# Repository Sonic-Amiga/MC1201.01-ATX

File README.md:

# О проекте

Данный проект является реконструкцией материнской платы ДВК-1 МС1201.01 в современных
условиях. Основной особенностью дизайна является замена большинства дефицитных микросхем на
более доступные схемотехнические решения, а также использование формата ATX.

Изначальным автором проекта является Павел "MAX232CPE". Данную плату можно
[приобрести у автора](https://www.avito.ru/ufa/tovary_dlya_kompyutera/ms1201_atx_3347565757?slocation=653240&context=H4sIAAAAAAAA_wE_AMD_YToyOntzOjEzOiJsb2NhbFByaW9yaXR5IjtiOjA7czoxOiJ4IjtzOjE2OiI1Sm9XZU1sOTdqZFBkbVNuIjt9T0K7ED8AAAA).
Целью данного репозитория является предоставление более читаемой схемы, чем предоставил автор,
а также её аудит с целью выявления ошибок. Целью не являлось создание собственной печатной платы, поэтому
посадочные места для компонентов не верифицировались, хотя должны быть назначены верно.

Нумерация элементов на схеме выполнена таким образом, что её можно сопоставить с оригинальной схемой.
Резисторные сборки разделены на дискретные резисторы, их нумерация E<номер сборки>_<номер контакта>. Элементы,
содержащие в своём названии букву X (напр. DX8, RX10, и т. д.) взяты из схемы замены динамического ОЗУ на
статическое.

В справочных целях все оригинальные схемы и некоторую документацию можно найти в каталоге [docs](docs). Схемы
приведены в нескольких версиях для лучшей читаемости.

# Обнаруженные ошибки (ERRATA) для ревизии 0.1c.

Некоторые из этих ошибок требуют реализации дополнительных схем. С этой целью разработана мезонинная плата,
которая содержит отсутствующую логику управления памятью, а также буфера для внешней шины. Документация на
плату доступна в каталоге [Mezzanine_Rev_0.1C](Mezzanine_Rev_0.1C).

Примечание: м/С 74HCT4067 может оказаться сложно найти. Успешно протестирована замена на гораздо более популярную
74HC4067. На AliExpress / Ozon также доступна микросхема CD4067 в DIP24 корпусе, но на данный момент её применение
не увенчалось успехом. Эта проблема будет разобрана позднее.

- E0001: Отсутствует подтяжка на +5В  
В оригинальной схеме данная цепь имеет номер 26 и подтянута к +5В через резисторную сборку E6 вывод 9.  
Решение: Установить резистор 2.2K навесным монтажом.

- E0002: Не подключенный вход /R микросхемы DD44  
В оригинальной схеме этот вход тоже не подключен, однако логика подсказывает, что на него также нужна подтяжка к +5В.  
Решение: Входы DD44 постоянно подтянуты к +5В. В оригинальной схеме МС1201.01 на них поданы сигналы с силовой
системной шины, которая в данном варианте удалена. Не устанавливать микросхему DD44 т. к. она ничего не делает.

- E0003: Неверное подключение /RPLY  
В оригинальной схеме глобальный сигнал /RPLY заведён на вывод 2 микросхемы DD8 через буфер К531АП2П. Буфер был
удалён автором реплики вместе с силовой шиной, а вместе с ним и соединение. Синхронизация сигнала /RPLY по любому
фронту тактового сигнала необходима согласно документации на процессор.  
Решение: Сигнал /RPLY соединяется через буфер DD1 на мезонинной плате. При необходимости можно запустить компьютер
без этого буфера, для этого необходимо не устанавливать E5_4 и соединить вывод 2 DD8 с глобальной цепью /RPLY.
Подтяжка сигнала /RPLY при этом осуществляется резистором E4_3.

- E0004: Отсутствует подключение CSRAM
Нет связи между выводом 10 DX7 и выводом 3 DX9, а также нет резистора RX10. Данный сигнал разрешает выбор ОЗУ.
Решение: провести отсутствующую связь и установить резистор навесным монтажом.  

- E0005: Не подключенные входы микросхем DD5 и DD9  
В оригинальной схеме сюда подаётся сигнал LOCK с контроллера динамической памяти. Этот сигнал разрешает обращение
к системному ПЗУ, активный уровень высокий и управляется регистром режима памяти (описан ниже).
Решение: Недостающая логика реализована на мезонинной плате.

- E0006: Дублированный резистор подтяжки  
Резистор должен быть только один, второй добавлен по ошибке.  
Решение: устанавливать только один из двух резисторов.

- E0007: Перепутаны типы микросхем на шелкографии
На плате перепутаны местами маркировки типов микросхем DD20 и DD44.  
Решение: Устанавливать согласно принципиальной схеме

- E0008: Отсутствует декодер адресов системного окна
В оригинальной схеме по адресам 177600..177677 доступны 64 байта ОЗУ, используемые процессором для переключения
между пользовательским и пультовым режимами. Данные адреса обусловлены аппаратным строением процессора и не могут
быть изменены. Этот функционал также реализуется удалённым контроллером динамической памяти. Для правильной работы
необходима дополнительная дешифрация адресных линий A9..A6 при доступе к области 176000...177777. Схема подключения
SRAM была перенесена с МС1201.02, которая имеет другой менеджер памяти, там данная область отсутствует.
Решение: Недостающая логика реализована на мезонинной плате.

- E0009: Вывод 8 микросхемы 1801ВП1-065 соединён с +5В
В оригинальной схеме используется микросхема 035, имеющая некоторые отличия. В частности, вывод 8 используется для
выбора 5-битного слова. В варианте 065 данный вывод является выходом с открытым коллектором, говорящим о том, что
микросхема выбрана. Соединение его с +5В может привести к повреждению микросхемы при попытке обращения к ней.
Решение: отключить вывод от +5В, перерезав дорожку. Сам вывод может быть использован для диагностики (требуется
подтяжка к +5В).

- E0010: Кнопка Reset подключена неверно.
Сигнал /INIT является для процессора выходом и презназначен для сброса внешних устройств и замыкание его на
землю не вызывает перезапуск процессора. Рестарт процессора осуществляется путём сброса сигналов /DCLO и /ACLO.
Решение: подключить кнопку параллельно конденсатору C76. Можно воспользоваться монтажным полем для установки
2-контактного разъёма.

- E0011: Некорректное соединение /DSR и /RxD.
Активным уровнем для этих сигналов является 0. Согласно спецификации сигнал DSR в активном состоянии говорит о том,
что удалённое устройство присутствует, включено и готово к работе. 155ЛН2 - это инверторы с открытым коллектором.
Установка сигнала /DSR в активное состояние приводит к тому, что линия RxD оказывается постоянно посаженной на 0,
что препятствует передаче данных.
Решение: разорвать соединение между выводами 10 и 12 микросхемы DX_16, разрезав дорожку.

# Карта памяти платы

Все адреса восьмеричные.

Начало | Конец  | Размер | Описание
-------|--------|--------|---------
000000 | 157777 | 56 Кб  | Основное ОЗУ
160000 | 163777 | 2 Кб   | Системное ПЗУ (если установлен бит 2 или 3 регистра режима памяти), иначе расширенное ОЗУ
164000 | 173777 | 3.5 Кб | Системное ПЗУ (если установлен бит 3 регистра режима памяти), иначе расширенное ОЗУ
173000 | 173777 | 512 б  | Системное ПЗУ (отображается всегда)
174000 | 175777 | 1 кб   | Расширенное ОЗУ
176000 | 176557 | 880 б  | Свободная область MMIO
176560 | 176567 | 8 б    | Второй последовательный порт
177560 | 177567 | 8 б    | Первый последовательный порт
177570 | 177577 | 8 б    | Свободная область MMIO
177600 | 177677 | 64 б   | Системное ОЗУ
177700 | 177716 | 16 б   | Внутренние регистры процессора (периферийный блок)
177714 |        |        | Внешний регистр ЦП 2 (/SEL2)
177716 |        |        | Внешний регистр ЦП 1 (/SEL1), регистр начального пуска, регистр режима памяти

Регистр 177716 используется одновременно для нескольких нужд и имеет следующую конфигурацию:

Бит    | 15 | 14 | 13 | 12 | 11 | 10 | 9 | 8 | 7 | 6 | 5 | 4 | 3  | 2  | 1 | 0
-------|----|----|----|----|----|----|---|---|---|---|---|---|----|----|---|---
Чтение | 1  | 1  | 1  | 0  | 0  | 0  | 0 | 0 | 0 | 0 | 0 | 0 |  a | M2 | b | c
Запись | -  | -  | -  | -  | -  | -  | - | - | - | - | - | - | M3 | M2 | - | -

- Биты 15 - 8 задают адрес начального пуска 160000.
- M3, M2 - биты регистра режима памяти
- a, b, c - биты, определяемые перемычками SA1. Если перемычка, соответствующая биту 3, не установлена, то
в позиции a будет считываться бит M3 регистра режима.

# Конфиурирование адресов ОЗУ

## Основное ОЗУ

Основное ОЗУ (адреса 000000 - 157777) разбито на банки по 8 Кб, каждый из которых может быть запрещён путём
установки перемычки J2. Если перемычка снята - банк доступен. Отключение банка требуется при установке
пользовательского ПЗУ, которое занимает тот же банк.

Обратный порядок перемычек обусловлен тем, что адреса передаются по шине в инвертированном виде.

Начало | Конец  | Биты 15..13 | Перемычка | Примечание
-------|--------|-------------|-----------|-----------
000000 | 017777 | 000         | 15-16     |
020000 | 037777 | 001         | 13-14     |
040000 | 057777 | 010         | 11-12     |
060000 | 077777 | 011         |  9-10     |
100000 | 117777 | 100         |  7-8      |
120000 | 137777 | 101         |  5-6      |
140000 | 157777 | 110         |  3-4      |
160000 | 177777 | 111         |  1-2      | Не устанавливать

## Расширенное ОЗУ

Расширенное ОЗУ (адреса 160000 - 175777) разбито на банки по 1 Кб, каждый из которых может быть запрещён путём
установки перемычки J1. Если перемычка снята - банк доступен. Формально по стандарту DEC адреса начиная с 160000
зарезервированы под внешние устройстка, поэтому отключение банка может потребоваться в случае
подключения внешних устройств, использующих те же адреса, что и банк.

Начало  | Конец  | Биты 12..10 | Перемычка | Примечание
--------|--------|-------------|-----------|-----------
160000  | 161777 | 000         | 15-16     |
162000  | 163777 | 001         | 13-14     |
164000  | 165777 | 010         | 11-12     |
166000  | 167777 | 011         |  9-10     |
170000  | 171777 | 100         |  7-8      |
172000  | 173777 | 101         |  5-6      | Доступно только 512 байтов, адреса 173000 - 173777 заняты ПЗУ
174000  | 175777 | 110         |  3-4      |
176000  | 177777 | 111         |  1-2      | Не устанавливать

## Перемычка J3

В данной плате схема подключения ОЗУ была полностью скопирована с существовавшей ранее универсальной схемы замены
ОЗУ для машин начиная с МС1202 (ДВК-2), поэтому в ней также присутствуют перемычки J3, предназначенные для адаптации
к различным машинам. В данной плате единственный вариант конфигурации предполагает соединение контактов 1 и 2. Это
соединение можно запаять жёстко, его переключение не предполагается. Остальные перемычки J3 использованию не подлежат,
поэтому разъём под них можно не устанавливать вовсе.

# Конфигурирование последовательного порта

Задание режимов работы последовательного порта производится перемычками S2. В таблицах ниже значение 0
соответствует установленной перемычке, 1 - снятой.

#### Перемычка 1-2 - выбор базового адреса и векторов прерывания
| Значение | Базовый адрес | Вектора прерывания приемника/передатчика |
|----------|---------------|------------------------------------------|
| 0        | 177560        | 060/064                                  |
| 1        | 176560        | 360/364                                  |

#### Выбор формата обмена по последовательному каналу
| Перемычка | 0                                | 1                              |
|-----------|----------------------------------|--------------------------------|
| 3-4       | 7 бит данных в слове             | 8 бит данных в слове           |
| 5-6       | формировать и проверять четность | не использовать бит четности   |
| 7-8       | контроль по четности             | контроль по нечетности         |

#### Перемычки 15-16, 13-14, 11-12, 9-10 - выбор скорости обмена по последовательному каналу
| Значение | Скорость обмена
|----------|----------------
| 0000     | 50
| 0001     | 75
| 0010     | 100
| 0011     | 150
| 0100     | 200
| 0101     | 300
| 0110     | 600
| 0111     | 1200
| 1000     | 2400
| 1001     | 4800
| 1010     | 9600
| 1011     | 19200
| 1100     | 57600
| 1101     | останов
| 1110     | останов
| 1111     | останов

Количество стоп-битов всегда равно двум, хотя при приёме проверяется только один. Для надёжной работы приёмника
рекомендуется выставлять на терминале 2 стоп-бита.

# Отладка

## Пошаговая отладка с помощью стенда.

Во время отладки я использовал [универсальную плату ввода-вывода](https://github.com/Sonic-Amiga/VersatileDebugBoard).
Тестовые сценарии к ней написаны на python и доступны в каталоге [Test_Scripts](Test_Scripts). Схема подключения
портов платы указана ниже. Все сигналы, если не указано иное, можно подать на системный разъём.

* Порт A0 - AD7...AD0
* Порт A1 - AD15...AD8
* Порт A2 - выходные сигналы управления:
    * bit0 - /SYNC
    * bit1 - /DIN - подавать на вывод 1 микросхемы DD6
    * bit2 - /DOUT
    * bit3 - /SEL1
* Порт C0 - Входные сигналы управления:
    * bit 0 - /RPLY

Блокировка процессора, если он уже установлен, осуществляется путём снятия перемычки S15 (/ACLO) и соединения вывода
29 процессора с землёй (через неё же). Сигнал /DCLO нужно оставить подключённым, иначе процессор не снимет 0 с линии
/INIT, заблокировав таким образом регистр управления памятью и последовательный порт.

Данные сценарии позволяют также проверить собранный [РЕ-мулятор](https://github.com/1801BM1/remul). При его подключении напрямую к стенду необходима
установка резисторов подтяжки к +5В сопротивлением 2.2К на все линии AD, а также на /RPLY. Вход /CE РЕ-мулятора
при этом соединяется с землёй.

!!! Учтите !!!, что К1801ВП1-065 реализует аппаратное управление потоком RTS/CTS. Если сигнал CTS от удалённого
устройства неактивен, то флаг готовности передатчика не выставляется, и тестовый сценарий будет бесконечно ждать
готовности, которая никогда не наступит. Дешёвые кабели USB-Serial могут не реализовывать эту линию. В этом случае
хотя-бы соедините RTS и CTS со стороны платы между собой (вам в любом случае понадобится нуль-модемный адаптер для
соединения с ПК с эмулятором терминала). То же самое относится и к работе программы из ПЗУ. Если вам кажется, что
машина висит, проверьте прохождение сигнала CTS.

## Тестирование с помощью тест-ПЗУ

Для финальной проверки и доводки собранной машины я написал специальное тест-ПЗУ. Его можно записать в РЕ-мулятор и
проверить вашу машину. Исходники доступны в каталоге [Test_ROM](Test_ROM).

Для сборки Вам потребуются:

* [Кросс-ассемблер MACRO-11](https://github.com/j-hoppe/MACRO11)
* [Линкер](https://github.com/AK6DN/obj2bin)
* [Утилита rev16.py](https://github.com/1801BM1/k1801/tree/master/rom/rev16_py)
* [Утилита srec_cat](https://srecord.sourceforge.net/)

Я собираю из-под Windows с использованием окружения MSYS2. Все вышеозначенные инструменты должны быть доступны в $PATH.

# Благодарности

* Павлу "MAX232CPE" за замечательный проект.
* 1801BM1@gmail.com за [исчерпывающую документацию на процессор](https://forum.maxiol.com/index.php?act=attach&type=post&id=10512).
* Oleksandr Kovalenko за [библиотеку элементов для KiCad](https://github.com/alk0v/KiCad-Lib-ussr-elements).
* Vslav за [документацию на К1801ВП1](https://github.com/1801BM1/k1801) и [проект РЕ-мулятора](https://github.com/1801BM1/remul).
* Jörg Hoppe за порт MACRO-11
* Don North за кросс-платформенный линковщик

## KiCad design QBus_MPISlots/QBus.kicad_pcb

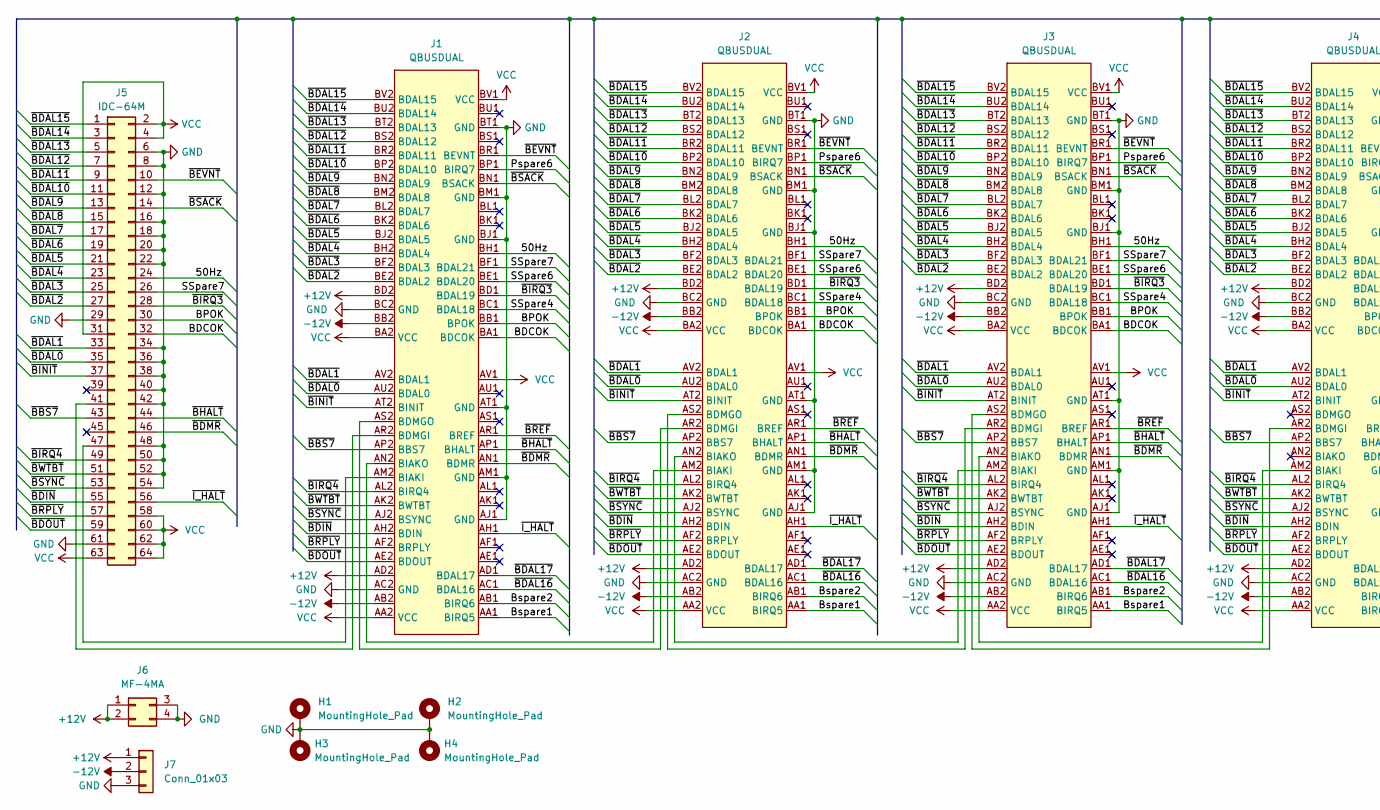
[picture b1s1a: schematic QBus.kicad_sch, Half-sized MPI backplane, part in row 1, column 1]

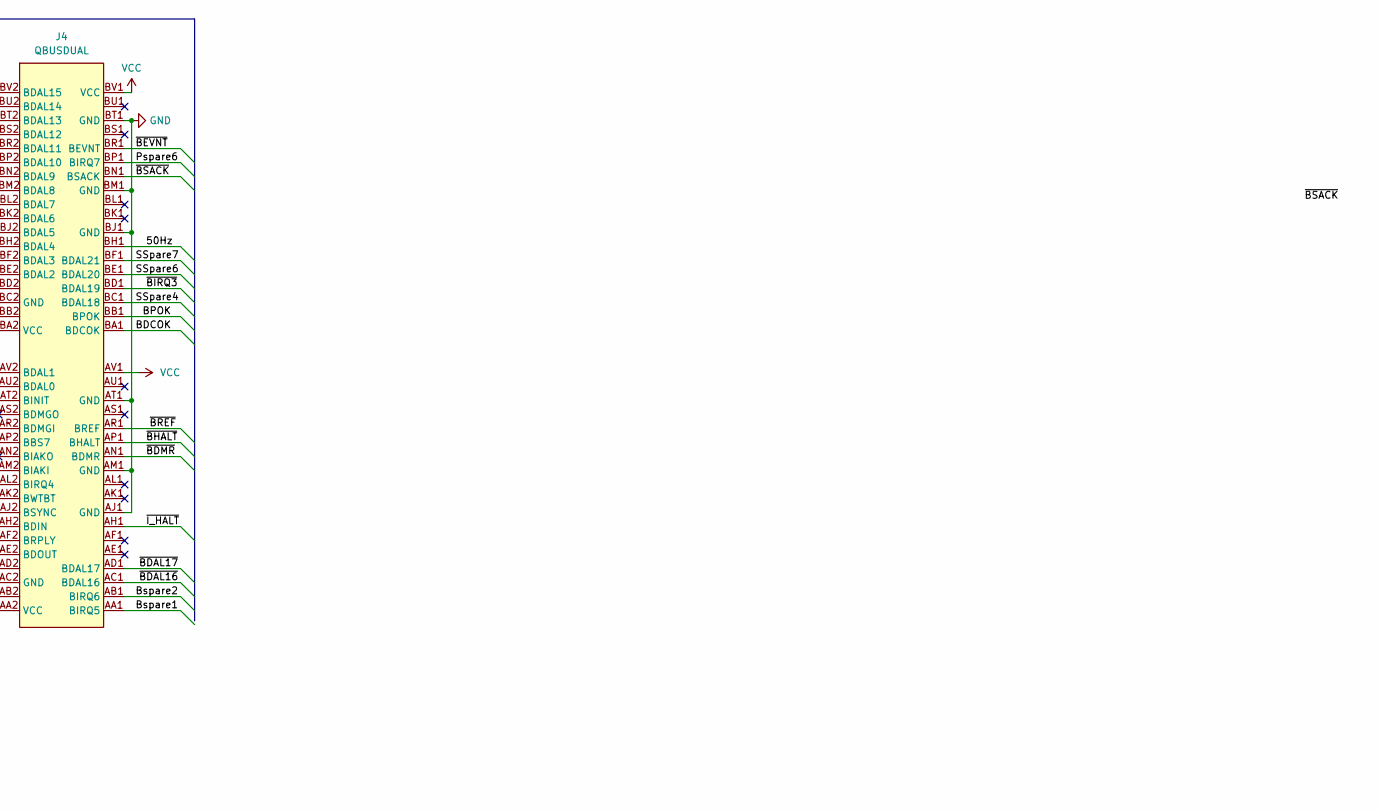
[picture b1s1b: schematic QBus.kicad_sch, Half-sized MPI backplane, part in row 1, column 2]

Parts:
H1, H2, H3, H4: MountingHole_Pad; MountingHole_3.5mm_Pad
J1, J2, J3, J4: QBUSDUAL; RPPM16x72
J5: IDC-64M; IDC-Header_2x32_P2.54mm_Vertical
J6: MF-4MA; Molex_Mini-Fit_Jr_5566-04A_2x02_P4.20mm_Vertical
J7: Conn_01x03; Wago_734-133_1x03_P3.50mm_Vertical

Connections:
+12V: J1.AD2, J1.BD2, J2.AD2, J2.BD2, J3.AD2, J3.BD2, J4.AD2, J4.BD2, J6.1, J6.2, J7.1
-12V: J1.AB2, J1.BB2, J2.AB2, J2.BB2, J3.AB2, J3.BB2, J4.AB2, J4.BB2, J7.2
/50Hz: J1.BH1, J2.BH1, J3.BH1, J4.BH1, J5.24
/BDCOK: J1.BA1 (BDCOK), J2.BA1 (BDCOK), J3.BA1 (BDCOK), J4.BA1 (BDCOK), J5.32
/BPOK: J1.BB1 (BPOK), J2.BB1 (BPOK), J3.BB1 (BPOK), J4.BB1 (BPOK), J5.30
/Bspare1: J1.AA1 (BIRQ5), J2.AA1 (BIRQ5), J3.AA1 (BIRQ5), J4.AA1 (BIRQ5)
/Bspare2: J1.AB1 (BIRQ6), J2.AB1 (BIRQ6), J3.AB1 (BIRQ6), J4.AB1 (BIRQ6)
/Pspare6: J1.BP1 (BIRQ7), J2.BP1 (BIRQ7), J3.BP1 (BIRQ7), J4.BP1 (BIRQ7)
/SSpare4: J1.BC1 (BDAL18), J2.BC1 (BDAL18), J3.BC1 (BDAL18), J4.BC1 (BDAL18)
/SSpare6: J1.BE1 (BDAL20), J2.BE1 (BDAL20), J3.BE1 (BDAL20), J4.BE1 (BDAL20)
/SSpare7: J1.BF1 (BDAL21), J2.BF1 (BDAL21), J3.BF1 (BDAL21), J4.BF1 (BDAL21), J5.26
/~BBS7: J1.AP2 (BBS7), J2.AP2 (BBS7), J3.AP2 (BBS7), J4.AP2 (BBS7), J5.43
/~BDAL0: J1.AU2 (BDAL0), J2.AU2 (BDAL0), J3.AU2 (BDAL0), J4.AU2 (BDAL0), J5.35
/~BDAL1: J1.AV2 (BDAL1), J2.AV2 (BDAL1), J3.AV2 (BDAL1), J4.AV2 (BDAL1), J5.33
/~BDAL2: J1.BE2 (BDAL2), J2.BE2 (BDAL2), J3.BE2 (BDAL2), J4.BE2 (BDAL2), J5.27
/~BDAL3: J1.BF2 (BDAL3), J2.BF2 (BDAL3), J3.BF2 (BDAL3), J4.BF2 (BDAL3), J5.25
/~BDAL4: J1.BH2 (BDAL4), J2.BH2 (BDAL4), J3.BH2 (BDAL4), J4.BH2 (BDAL4), J5.23
/~BDAL5: J1.BJ2 (BDAL5), J2.BJ2 (BDAL5), J3.BJ2 (BDAL5), J4.BJ2 (BDAL5), J5.21
/~BDAL6: J1.BK2 (BDAL6), J2.BK2 (BDAL6), J3.BK2 (BDAL6), J4.BK2 (BDAL6), J5.19
/~BDAL7: J1.BL2 (BDAL7), J2.BL2 (BDAL7), J3.BL2 (BDAL7), J4.BL2 (BDAL7), J5.17
/~BDAL8: J1.BM2 (BDAL8), J2.BM2 (BDAL8), J3.BM2 (BDAL8), J4.BM2 (BDAL8), J5.15
/~BDAL9: J1.BN2 (BDAL9), J2.BN2 (BDAL9), J3.BN2 (BDAL9), J4.BN2 (BDAL9), J5.13
/~BDAL10: J1.BP2 (BDAL10), J2.BP2 (BDAL10), J3.BP2 (BDAL10), J4.BP2 (BDAL10), J5.11
/~BDAL11: J1.BR2 (BDAL11), J2.BR2 (BDAL11), J3.BR2 (BDAL11), J4.BR2 (BDAL11), J5.9
/~BDAL12: J1.BS2 (BDAL12), J2.BS2 (BDAL12), J3.BS2 (BDAL12), J4.BS2 (BDAL12), J5.7
/~BDAL13: J1.BT2 (BDAL13), J2.BT2 (BDAL13), J3.BT2 (BDAL13), J4.BT2 (BDAL13), J5.5
/~BDAL14: J1.BU2 (BDAL14), J2.BU2 (BDAL14), J3.BU2 (BDAL14), J4.BU2 (BDAL14), J5.3
/~BDAL15: J1.BV2 (BDAL15), J2.BV2 (BDAL15), J3.BV2 (BDAL15), J4.BV2 (BDAL15), J5.1
/~BDAL16: J1.AC1 (BDAL16), J2.AC1 (BDAL16), J3.AC1 (BDAL16), J4.AC1 (BDAL16)
/~BDAL17: J1.AD1 (BDAL17), J2.AD1 (BDAL17), J3.AD1 (BDAL17), J4.AD1 (BDAL17)
/~BDIN: J1.AH2 (BDIN), J2.AH2 (BDIN), J3.AH2 (BDIN), J4.AH2 (BDIN), J5.55
/~BDMR: J1.AN1 (BDMR), J2.AN1 (BDMR), J3.AN1 (BDMR), J4.AN1 (BDMR), J5.46
/~BDOUT: J1.AE2 (BDOUT), J2.AE2 (BDOUT), J3.AE2 (BDOUT), J4.AE2 (BDOUT), J5.59
/~BEVNT: J1.BR1 (BEVNT), J2.BR1 (BEVNT), J3.BR1 (BEVNT), J4.BR1 (BEVNT), J5.10
/~BHALT: J1.AP1 (BHALT), J2.AP1 (BHALT), J3.AP1 (BHALT), J4.AP1 (BHALT), J5.44
/~BINIT: J1.AT2 (BINIT), J2.AT2 (BINIT), J3.AT2 (BINIT), J4.AT2 (BINIT), J5.37
/~BIRQ3: J1.BD1 (BDAL19), J2.BD1 (BDAL19), J3.BD1 (BDAL19), J4.BD1 (BDAL19), J5.28
/~BIRQ4: J1.AL2 (BIRQ4), J2.AL2 (BIRQ4), J3.AL2 (BIRQ4), J4.AL2 (BIRQ4), J5.49
/~BREF: J1.AR1 (BREF), J2.AR1 (BREF), J3.AR1 (BREF), J4.AR1 (BREF)
/~BRPLY: J1.AF2 (BRPLY), J2.AF2 (BRPLY), J3.AF2 (BRPLY), J4.AF2 (BRPLY), J5.57
/~BSACK: J1.BN1 (BSACK), J2.BN1 (BSACK), J3.BN1 (BSACK), J4.BN1 (BSACK), J5.14
/~BSYNC: J1.AJ2 (BSYNC), J2.AJ2 (BSYNC), J3.AJ2 (BSYNC), J4.AJ2 (BSYNC), J5.53
/~BWTBT: J1.AK2 (BWTBT), J2.AK2 (BWTBT), J3.AK2 (BWTBT), J4.AK2 (BWTBT), J5.51
/~I_HALT: J1.AH1, J2.AH1, J3.AH1, J4.AH1, J5.56
GND: H1.1 (1_1), H2.1 (1_1), H3.1 (1_1), H4.1 (1_1), J1.AC2 (GND), J1.AJ1 (GND), J1.AM1 (GND), J1.AT1 (GND), J1.BC2 (GND), J1.BJ1 (GND), J1.BM1 (GND), J1.BT1 (GND), J2.AC2 (GND), J2.AJ1 (GND), J2.AM1 (GND), J2.AT1 (GND), J2.BC2 (GND), J2.BJ1 (GND), J2.BM1 (GND), J2.BT1 (GND), J3.AC2 (GND), J3.AJ1 (GND), J3.AM1 (GND), J3.AT1 (GND), J3.BC2 (GND), J3.BJ1 (GND), J3.BM1 (GND), J3.BT1 (GND), J4.AC2 (GND), J4.AJ1 (GND), J4.AM1 (GND), J4.AT1 (GND), J4.BC2 (GND), J4.BJ1 (GND), J4.BM1 (GND), J4.BT1 (GND), J5.6, J5.8, J5.12, J5.16, J5.18, J5.20, J5.22, J5.29, J5.34, J5.36, J5.38, J5.40, J5.42, J5.48, J5.50, J5.52, J5.54, J5.61, J6.3, J6.4, J7.3
unnamed: J1.AR2 (BDMGI), J5.41
unnamed: J1.AS2 (BDMGO), J2.AR2 (BDMGI)
unnamed: J1.AM2 (BIAKI), J5.47
unnamed: J1.AN2 (BIAKO), J2.AM2 (BIAKI)
unnamed: J2.AS2 (BDMGO), J3.AR2 (BDMGI)
unnamed: J2.AN2 (BIAKO), J3.AM2 (BIAKI)
unnamed: J3.AS2 (BDMGO), J4.AR2 (BDMGI)
unnamed: J3.AN2 (BIAKO), J4.AM2 (BIAKI)
VCC: J1.AA2 (VCC), J1.AV1, J1.BA2 (VCC), J1.BV1 (VCC), J2.AA2 (VCC), J2.AV1, J2.BA2 (VCC), J2.BV1 (VCC), J3.AA2 (VCC), J3.AV1, J3.BA2 (VCC), J3.BV1 (VCC), J4.AA2 (VCC), J4.AV1, J4.BA2 (VCC), J4.BV1 (VCC), J5.2, J5.4, J5.31, J5.58, J5.60, J5.62, J5.63, J5.64

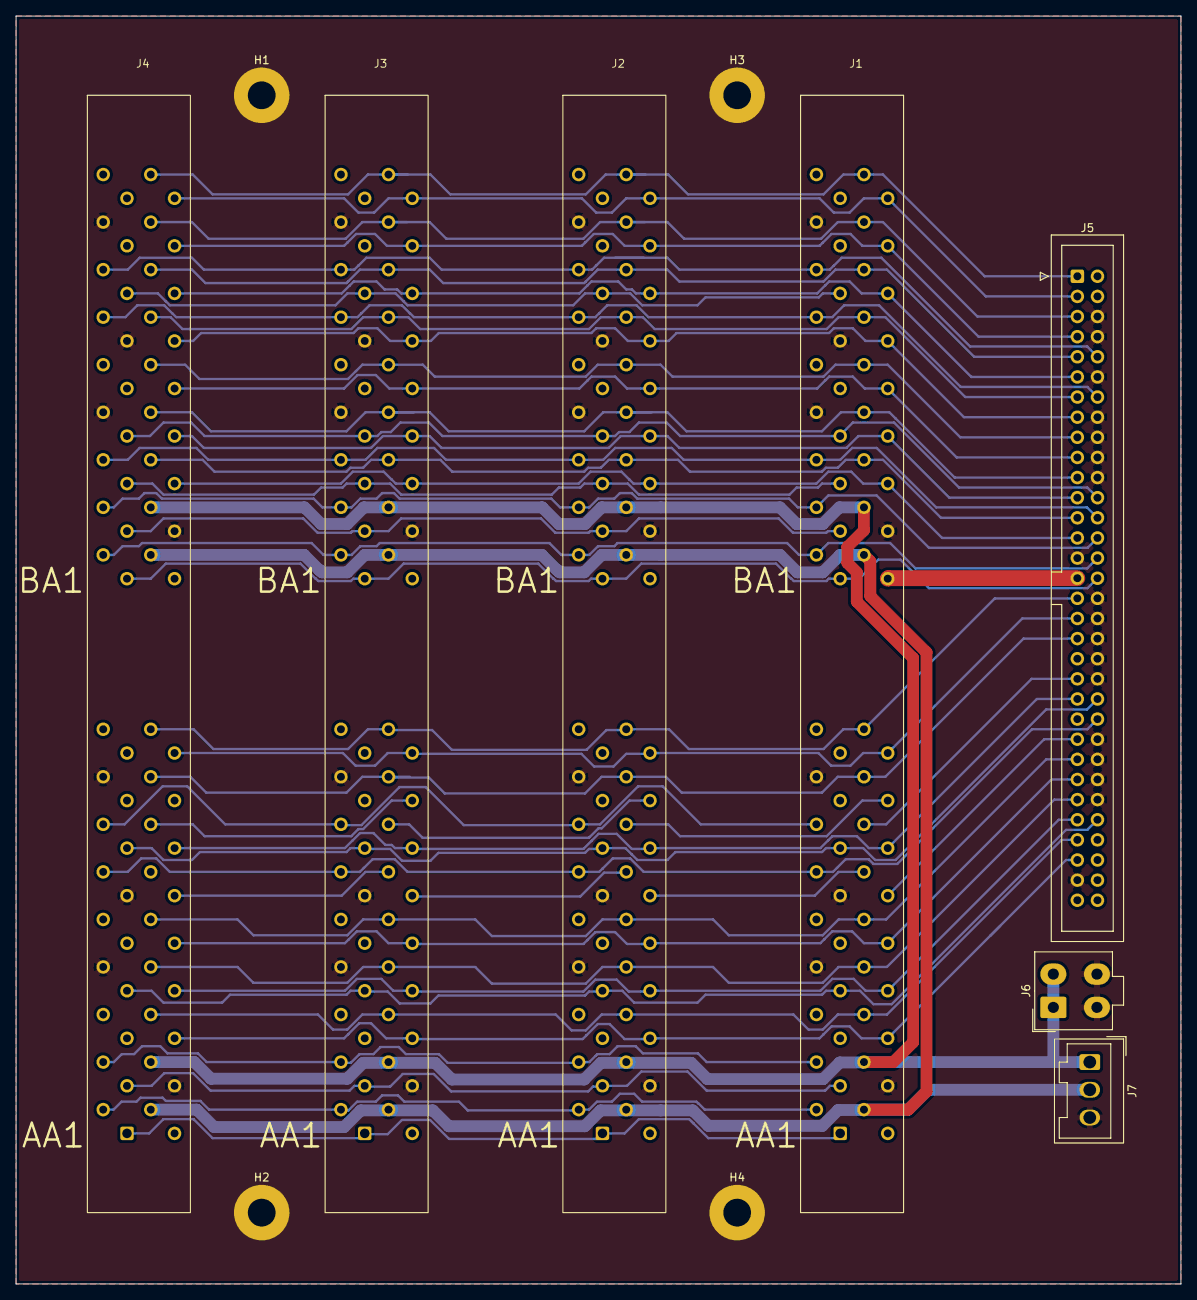
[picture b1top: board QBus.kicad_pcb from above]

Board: 2 copper layers, 147.0 x 160.0 mm, 11 parts (0 on the bottom side), 54 nets.

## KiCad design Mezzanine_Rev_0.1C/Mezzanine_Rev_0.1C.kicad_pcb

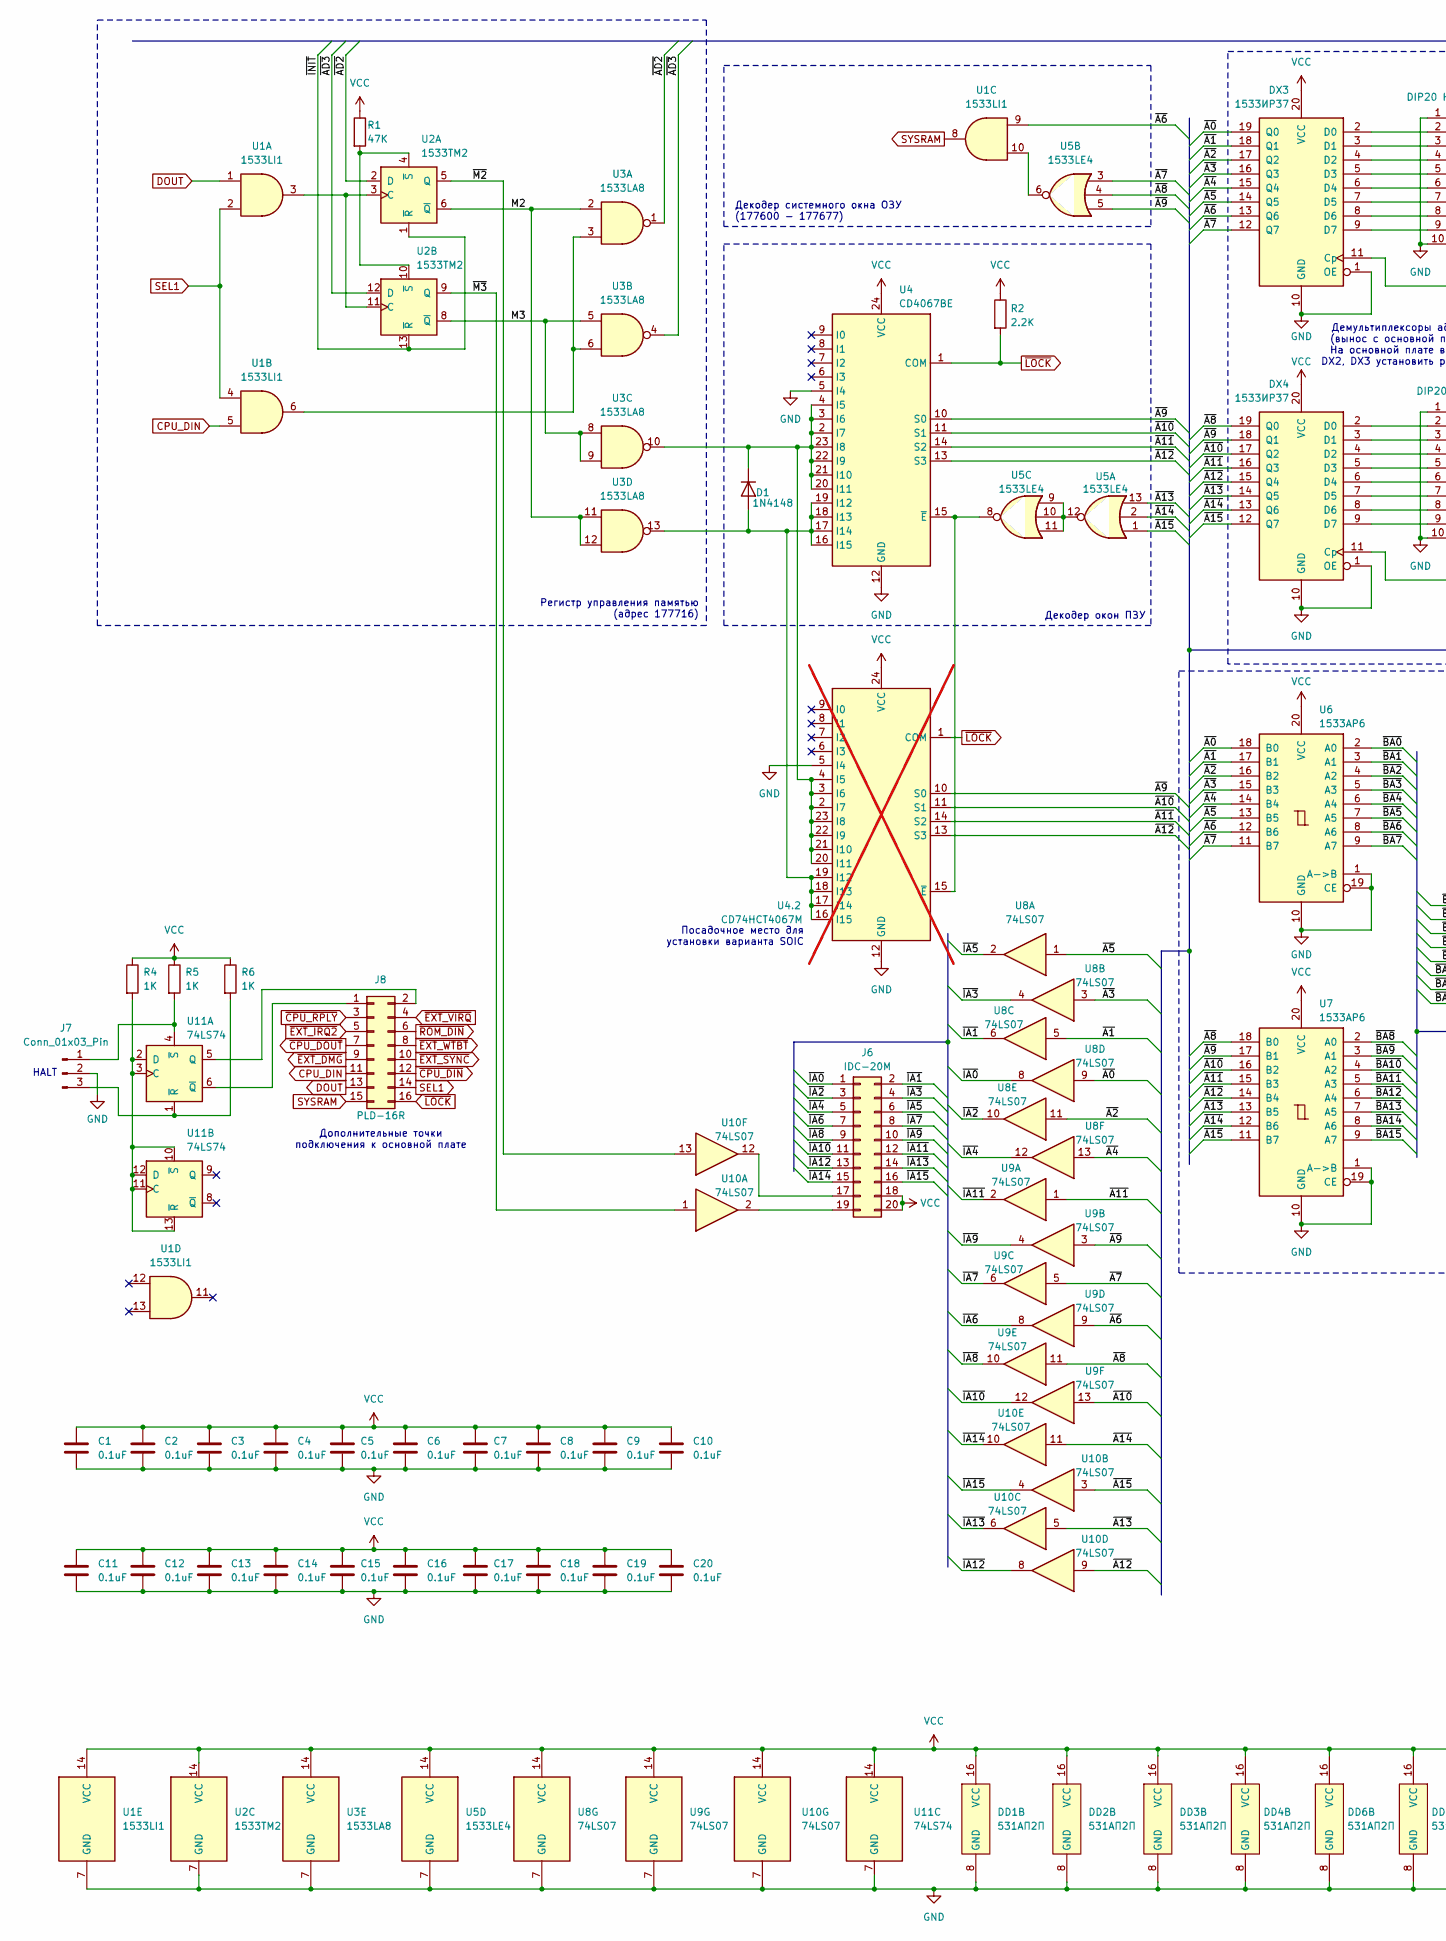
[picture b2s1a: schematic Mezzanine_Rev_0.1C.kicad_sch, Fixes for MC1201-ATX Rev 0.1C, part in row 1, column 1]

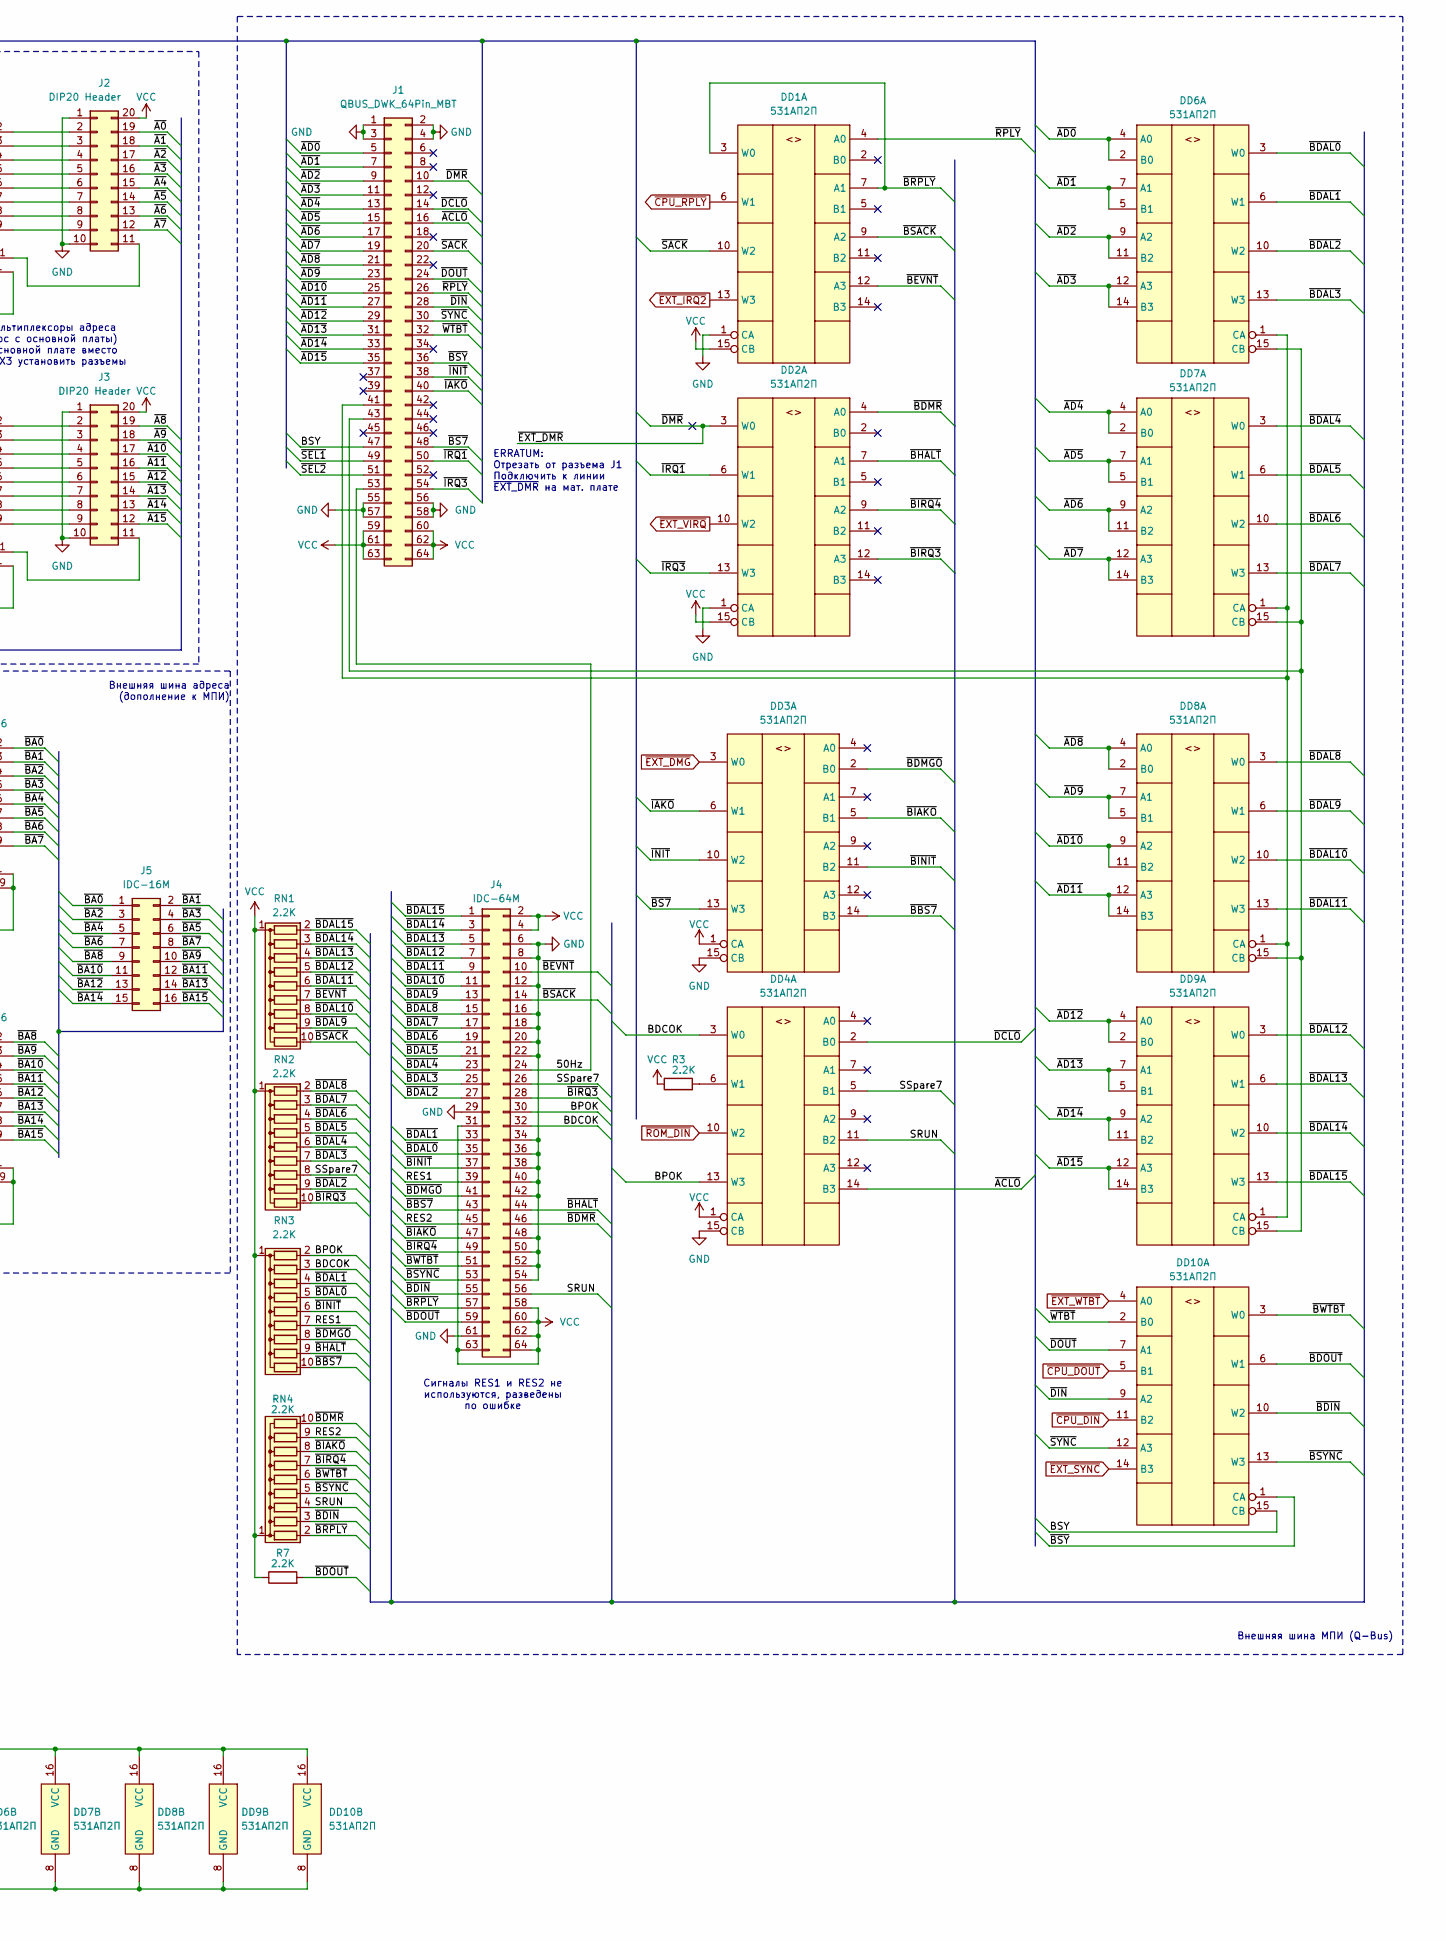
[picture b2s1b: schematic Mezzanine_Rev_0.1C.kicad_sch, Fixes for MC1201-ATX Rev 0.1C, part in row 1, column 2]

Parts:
C1, C2, C3, C4, C5, C6, C7, C8, C9, C10, C11, C12, C13, C14, C15, C16, C17, C18, C19, C20: 0.1uF; C_Disc_D6.0mm_W2.5mm_P5.00mm
D1: 1N4148; D_DO-35_SOD27_P7.62mm_Horizontal
DD1, DD2, DD3, DD4, DD6, DD7, DD8, DD9, DD10: 531АП2П; DIP-16_W7.62mm
DX3, DX4: 1533ИР37; DIP-20_W7.62mm
J1: QBUS_DWK_64Pin_MBT; PinSocket_2x32_P2.54mm_Vertical
J2, J3: DIP20 Header; DIP-Header-20_W7.62mm
J4: IDC-64M; IDC-Header_2x32_P2.54mm_Vertical
J5: IDC-16M; IDC-Header_2x08_P2.54mm_Vertical
J6: IDC-20M; IDC-Header_2x10_P2.54mm_Vertical
J7: Conn_01x03_Pin; PinHeader_1x03_P2.54mm_Vertical
J8: PLD-16R; PinHeader_2x08_P2.54mm_Horizontal
R1: 47K; R_Axial_DIN0204_L3.6mm_D1.6mm_P7.62mm_Horizontal
R2, R3, R7: 2.2K; R_Axial_DIN0204_L3.6mm_D1.6mm_P7.62mm_Horizontal
R4, R5, R6: 1K; R_Axial_DIN0204_L3.6mm_D1.6mm_P7.62mm_Horizontal
RN1, RN2, RN3, RN4: 2.2K; R_Array_SIP10
U1: 1533LI1; DIP-14_W7.62mm
U2: 1533TM2; DIP-14_W7.62mm
U3: 1533LA8; DIP-14_W7.62mm
U4: CD4067BE; DIP-24_W15.24mm
U4.2: CD74HCT4067M; SOIC-24W_7.5x15.4mm_P1.27mm; not fitted
U5: 1533LE4; DIP-14_W7.62mm
U6, U7: 1533AP6; DIP-20_W7.62mm
U8, U9, U10: 74LS07; DIP-14_W7.62mm
U11: 74LS74; DIP-14_W7.62mm

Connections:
/50Hz: J1.53, J4.24
/BDCOK: DD4.3 (W0), J4.32, RN3.3 (R2)
/BPOK: DD4.13 (W3), J4.30, RN3.2 (R1)
/BSY: DD10.15 (CB), J1.47
/M2: U2.6 (~Q), U3.2, U3.11, U3.12
/M3: U2.8 (~Q), U3.5, U3.8, U3.9
/RES1: J4.39, RN3.7 (R6)
/RES2: J4.45, RN4.9 (R8)
/SRUN: DD4.11 (B2), J4.56, RN4.4 (R3)
/SSpare7: DD4.5 (B1), J4.26, RN2.8 (R7)
/~A0: DX3.19 (Q0), J2.19, U6.18 (B0), U8.9
/~A1: DX3.18 (Q1), J2.18, U6.17 (B1), U8.5
/~A2: DX3.17 (Q2), J2.17, U6.16 (B2), U8.11
/~A3: DX3.16 (Q3), J2.16, U6.15 (B3), U8.3
/~A4: DX3.15 (Q4), J2.15, U6.14 (B4), U8.13
/~A5: DX3.14 (Q5), J2.14, U6.13 (B5), U8.1
/~A6: DX3.13 (Q6), J2.13, U1.9, U6.12 (B6), U9.9
/~A7: DX3.12 (Q7), J2.12, U5.3, U6.11 (B7), U9.5
/~A8: DX4.19 (Q0), J3.19, U5.4, U7.18 (B0), U9.11
/~A9: DX4.18 (Q1), J3.18, U4.10 (S0), U4.2.10 (S0), U5.5, U7.17 (B1), U9.3
/~A10: DX4.17 (Q2), J3.17, U4.11 (S1), U4.2.11 (S1), U7.16 (B2), U9.13
/~A11: DX4.16 (Q3), J3.16, U4.14 (S2), U4.2.14 (S2), U7.15 (B3), U9.1
/~A12: DX4.15 (Q4), J3.15, U4.13 (S3), U4.2.13 (S3), U7.14 (B4), U10.9
/~A13: DX4.14 (Q5), J3.14, U5.13, U7.13 (B5), U10.5
/~A14: DX4.13 (Q6), J3.13, U5.2, U7.12 (B6), U10.11
/~A15: DX4.12 (Q7), J3.12, U5.1, U7.11 (B7), U10.3
/~ACLO: DD4.14 (B3), J1.16
/~AD0: DD6.2 (B0), DD6.4 (A0), J1.5
/~AD1: DD6.5 (B1), DD6.7 (A1), J1.7
/~AD2: DD6.9 (A2), DD6.11 (B2), J1.9, U2.2 (D), U3.1
/~AD3: DD6.12 (A3), DD6.14 (B3), J1.11, U2.12 (D), U3.4
/~AD4: DD7.2 (B0), DD7.4 (A0), J1.13
/~AD5: DD7.5 (B1), DD7.7 (A1), J1.15
/~AD6: DD7.9 (A2), DD7.11 (B2), J1.17
/~AD7: DD7.12 (A3), DD7.14 (B3), J1.19
/~AD8: DD8.2 (B0), DD8.4 (A0), J1.21
/~AD9: DD8.5 (B1), DD8.7 (A1), J1.23
/~AD10: DD8.9 (A2), DD8.11 (B2), J1.25
/~AD11: DD8.12 (A3), DD8.14 (B3), J1.27
/~AD12: DD9.2 (B0), DD9.4 (A0), J1.29
/~AD13: DD9.5 (B1), DD9.7 (A1), J1.31
/~AD14: DD9.9 (A2), DD9.11 (B2), J1.33
/~AD15: DD9.12 (A3), DD9.14 (B3), J1.35
/~BA0: J5.1, U6.2 (A0)
/~BA1: J5.2, U6.3 (A1)
/~BA2: J5.3, U6.4 (A2)
/~BA3: J5.4, U6.5 (A3)
/~BA4: J5.5, U6.6 (A4)
/~BA5: J5.6, U6.7 (A5)
/~BA6: J5.7, U6.8 (A6)
/~BA7: J5.8, U6.9 (A7)
/~BA8: J5.9, U7.2 (A0)
/~BA9: J5.10, U7.3 (A1)
/~BA10: J5.11, U7.4 (A2)
/~BA11: J5.12, U7.5 (A3)
/~BA12: J5.13, U7.6 (A4)
/~BA13: J5.14, U7.7 (A5)
/~BA14: J5.15, U7.8 (A6)
/~BA15: J5.16, U7.9 (A7)
/~BBS7: DD3.14 (B3), J4.43, RN3.10 (R9)
/~BDAL0: DD6.3 (W0), J4.35, RN3.5 (R4)
/~BDAL1: DD6.6 (W1), J4.33, RN3.4 (R3)
/~BDAL2: DD6.10 (W2), J4.27, RN2.9 (R8)
/~BDAL3: DD6.13 (W3), J4.25, RN2.7 (R6)
/~BDAL4: DD7.3 (W0), J4.23, RN2.6 (R5)
/~BDAL5: DD7.6 (W1), J4.21, RN2.5 (R4)
/~BDAL6: DD7.10 (W2), J4.19, RN2.4 (R3)
/~BDAL7: DD7.13 (W3), J4.17, RN2.3 (R2)
/~BDAL8: DD8.3 (W0), J4.15, RN2.2 (R1)
/~BDAL9: DD8.6 (W1), J4.13, RN1.9 (R8)
/~BDAL10: DD8.10 (W2), J4.11, RN1.8 (R7)
/~BDAL11: DD8.13 (W3), J4.9, RN1.6 (R5)
/~BDAL12: DD9.3 (W0), J4.7, RN1.5 (R4)
/~BDAL13: DD9.6 (W1), J4.5, RN1.4 (R3)
/~BDAL14: DD9.10 (W2), J4.3, RN1.3 (R2)
/~BDAL15: DD9.13 (W3), J4.1, RN1.2 (R1)
/~BDIN: DD10.10 (W2), J4.55, RN4.3 (R2)
/~BDMGO: DD3.2 (B0), J4.41, RN3.8 (R7)
/~BDMR: DD2.4 (A0), J4.46, RN4.10 (R9)
/~BDOUT: DD10.6 (W1), J4.59, R7.2
/~BEVNT: DD1.12 (A3), J4.10, RN1.7 (R6)
/~BHALT: DD2.7 (A1), J4.44, RN3.9 (R8)
/~BIAKO: DD3.5 (B1), J4.47, RN4.8 (R7)
/~BINIT: DD3.11 (B2), J4.37, RN3.6 (R5)
/~BIRQ3: DD2.12 (A3), J4.28, RN2.10 (R9)
/~BIRQ4: DD2.9 (A2), J4.49, RN4.7 (R6)
/~BRPLY: DD1.3 (W0), DD1.7 (A1), J4.57, RN4.2 (R1)
/~BS7: DD3.13 (W3), J1.48
/~BSACK: DD1.9 (A2), J4.14, RN1.10 (R9)
/~BSYNC: DD10.13 (W3), J4.53, RN4.5 (R4)
/~BSY: DD10.1 (CA), J1.36
/~BWTBT: DD10.3 (W0), J4.51, RN4.6 (R5)
/~DCLO: DD4.2 (B0), J1.14
/~DIN: DD10.9 (A2), J1.28
/~DMR: DD2.3 (W0), J1.10
/~DOUT: DD10.7 (A1), J1.24
/~IA0: J6.1, U8.8
/~IA1: J6.2, U8.6
/~IA2: J6.3, U8.10
/~IA3: J6.4, U8.4
/~IA4: J6.5, U8.12
/~IA5: J6.6, U8.2
/~IA6: J6.7, U9.8
/~IA7: J6.8, U9.6
/~IA8: J6.9, U9.10
/~IA9: J6.10, U9.4
/~IA10: J6.11, U9.12
/~IA11: J6.12, U9.2
/~IA12: J6.13, U10.8
/~IA13: J6.14, U10.6
/~IA14: J6.15, U10.10
/~IA15: J6.16, U10.4
/~IAKO: DD3.6 (W1), J1.40
/~INIT: DD3.10 (W2), J1.38, U2.1 (~R), U2.13 (~R)
/~IRQ1: DD2.6 (W1), J1.50
/~IRQ3: DD2.13 (W3), J1.54
/~M2: U2.5 (Q), U10.13
/~M3: U2.9 (Q), U10.1
/~RPLY: DD1.4 (A0), J1.26
/~SACK: DD1.10 (W2), J1.20
/~SEL1: J1.49
/~SEL2: J1.51
/~SYNC: DD10.12 (A3), J1.30
/~WTBT: DD10.2 (B0), J1.32
CPU_DIN: J8.11, U1.5
DOUT: J8.13, U1.1
GND: C1.2, C2.2, C3.2, C4.2, C5.2, C6.2, C7.2, C8.2, C9.2, C10.2, C11.2, C12.2, C13.2, C14.2, C15.2, C16.2, C17.2, C18.2, C19.2, C20.2, DD1.1 (CA), DD1.8 (GND), DD2.1 (CA), DD2.8 (GND), DD3.8 (GND), DD3.15 (CB), DD4.8 (GND), DD4.15 (CB), DD6.8 (GND), DD7.8 (GND), DD8.8 (GND), DD9.8 (GND), DD10.8 (GND), DX3.1 (OE), DX3.10 (GND), DX4.1 (OE), DX4.10 (GND), J1.1, J1.2, J1.3, J1.4, J1.55, J1.56, J1.57, J1.58, J2.1, J2.10, J3.1, J3.10, J4.6, J4.8, J4.12, J4.16, J4.18, J4.20, J4.22, J4.29, J4.34, J4.36, J4.38, J4.40, J4.42, J4.48, J4.50, J4.52, J4.54, J4.61, J7.2, U1.7 (GND), U2.7 (GND), U3.7 (GND), U4.5 (I4), U4.12 (GND), U4.2.5 (I4), U4.2.12 (GND), U5.7 (GND), U6.1 (A->B), U6.10 (GND), U6.19 (CE), U7.1 (A->B)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
unnamed: D1.2 (A), U3.13, U4.16 (I15), U4.17 (I14), U4.18 (I13), U4.19 (I12), U4.2.16 (I15), U4.2.17 (I14), U4.2.18 (I13), U4.2.19 (I12)
unnamed: D1.1 (K), U3.10, U4.2 (I7), U4.3 (I6), U4.4 (I5), U4.20 (I11), U4.21 (I10), U4.22 (I9), U4.23 (I8), U4.2.2 (I7), U4.2.3 (I6), U4.2.4 (I5), U4.2.20 (I11), U4.2.21 (I10), U4.2.22 (I9), U4.2.23 (I8)
unnamed: DD4.6 (W1), R3.2
unnamed: DD6.1 (CA), DD7.1 (CA), DD8.1 (CA), DD9.1 (CA), J1.41
unnamed: DD6.15 (CB), DD7.15 (CB), DD8.15 (CB), DD9.15 (CB), J1.43
unnamed: DX3.11 (Cp), J2.11
unnamed: DX3.2 (D0), J2.2
unnamed: DX3.3 (D1), J2.3
unnamed: DX3.4 (D2), J2.4
unnamed: DX3.5 (D3), J2.5
unnamed: DX3.6 (D4), J2.6
unnamed: DX3.7 (D5), J2.7
unnamed: DX3.8 (D6), J2.8
unnamed: DX3.9 (D7), J2.9
unnamed: DX4.11 (Cp), J3.11
unnamed: DX4.2 (D0), J3.2
unnamed: DX4.3 (D1), J3.3
unnamed: DX4.4 (D2), J3.4
unnamed: DX4.5 (D3), J3.5
unnamed: DX4.6 (D4), J3.6
unnamed: DX4.7 (D5), J3.7
unnamed: DX4.8 (D6), J3.8
unnamed: DX4.9 (D7), J3.9
unnamed: J6.17, U10.12
unnamed: J6.19, U10.2
unnamed: J7.1, R5.2, U11.4 (~S)
unnamed: J7.3, R6.2, U11.1 (~R)
unnamed: J8.1, U11.6 (~Q)
unnamed: J8.2, U11.5 (Q)
unnamed: U1.6, U3.3, U3.6
unnamed: U1.10, U5.6
unnamed: U1.3, U2.3 (C), U2.11 (C)
unnamed: R1.2, U2.4 (~S), U2.10 (~S)
unnamed: U4.15 (~E), U4.2.15 (~E), U5.8
unnamed: U5.9, U5.10, U5.11, U5.12
unnamed: R4.2, U11.2 (D), U11.3 (C), U11.10 (~S), U11.11 (C), U11.12 (D), U11.13 (~R)
SEL1: J8.14, U1.2, U1.4
SYSRAM: J8.15, U1.8
VCC: C1.1, C2.1, C3.1, C4.1, C5.1, C6.1, C7.1, C8.1, C9.1, C10.1, C11.1, C12.1, C13.1, C14.1, C15.1, C16.1, C17.1, C18.1, C19.1, C20.1, DD1.15 (CB), DD1.16 (VCC), DD2.15 (CB), DD2.16 (VCC), DD3.1 (CA), DD3.16 (VCC), DD4.1 (CA), DD4.16 (VCC), DD6.16 (VCC), DD7.16 (VCC), DD8.16 (VCC), DD9.16 (VCC), DD10.16 (VCC), DX3.20 (VCC), DX4.20 (VCC), J1.59, J1.60, J1.61, J1.62, J1.63, J1.64, J2.20, J3.20, J4.2, J4.4, J4.31, J4.58, J4.60, J4.62, J4.63, J4.64, J6.18, J6.20, R1.1, R2.1, R3.1, R4.1, R5.1, R6.1, R7.1, RN1.1 (common), RN2.1 (common), RN3.1 (common), RN4.1 (common), U1.14 (VCC), U2.14 (VCC), U3.14 (VCC), U4.24 (VCC), U4.2.24 (VCC), U5.14 (VCC), U6.20 (VCC), U7.20 (VCC), U8.14 (VCC), U9.14 (VCC), U10.14 (VCC), U11.14 (VCC)
~CPU_DIN: DD10.11 (B2), J8.12
~CPU_DOUT: DD10.5 (B1), J8.7
~CPU_RPLY: DD1.6 (W1), J8.3
~EXT_DMG: DD3.3 (W0), J8.9
~EXT_IRQ2: DD1.13 (W3), J8.5
~EXT_SYNC: DD10.14 (B3), J8.10
~EXT_VIRQ: DD2.10 (W2), J8.4
~EXT_WTBT: DD10.4 (A0), J8.8
~LOCK: J8.16, R2.2, U4.1 (COM), U4.2.1 (COM)
~ROM_DIN: DD4.10 (W2), J8.6

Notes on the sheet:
Посадочное место для установки варианта SOIC
ERRATUM: Отрезать от разъема J1 Подключить к линии ~{EXT_DMR} на мат. плате
Сигналы RES1 и RES2 не используются, разведены по ошибке
HALT
Внешняя шина МПИ (Q-Bus)
Дополнительные точки подключения к основной плате
Регистр управления памятью (адрес 177716)
Декодер окон ПЗУ
Декодер системного окна ОЗУ (177600 - 177677)
Демультиплексоры адреса (вынос с основной платы) На основной плате вместо DX2, DX3 установить разъемы
Внешняя шина адреса (дополнение к МПИ)
